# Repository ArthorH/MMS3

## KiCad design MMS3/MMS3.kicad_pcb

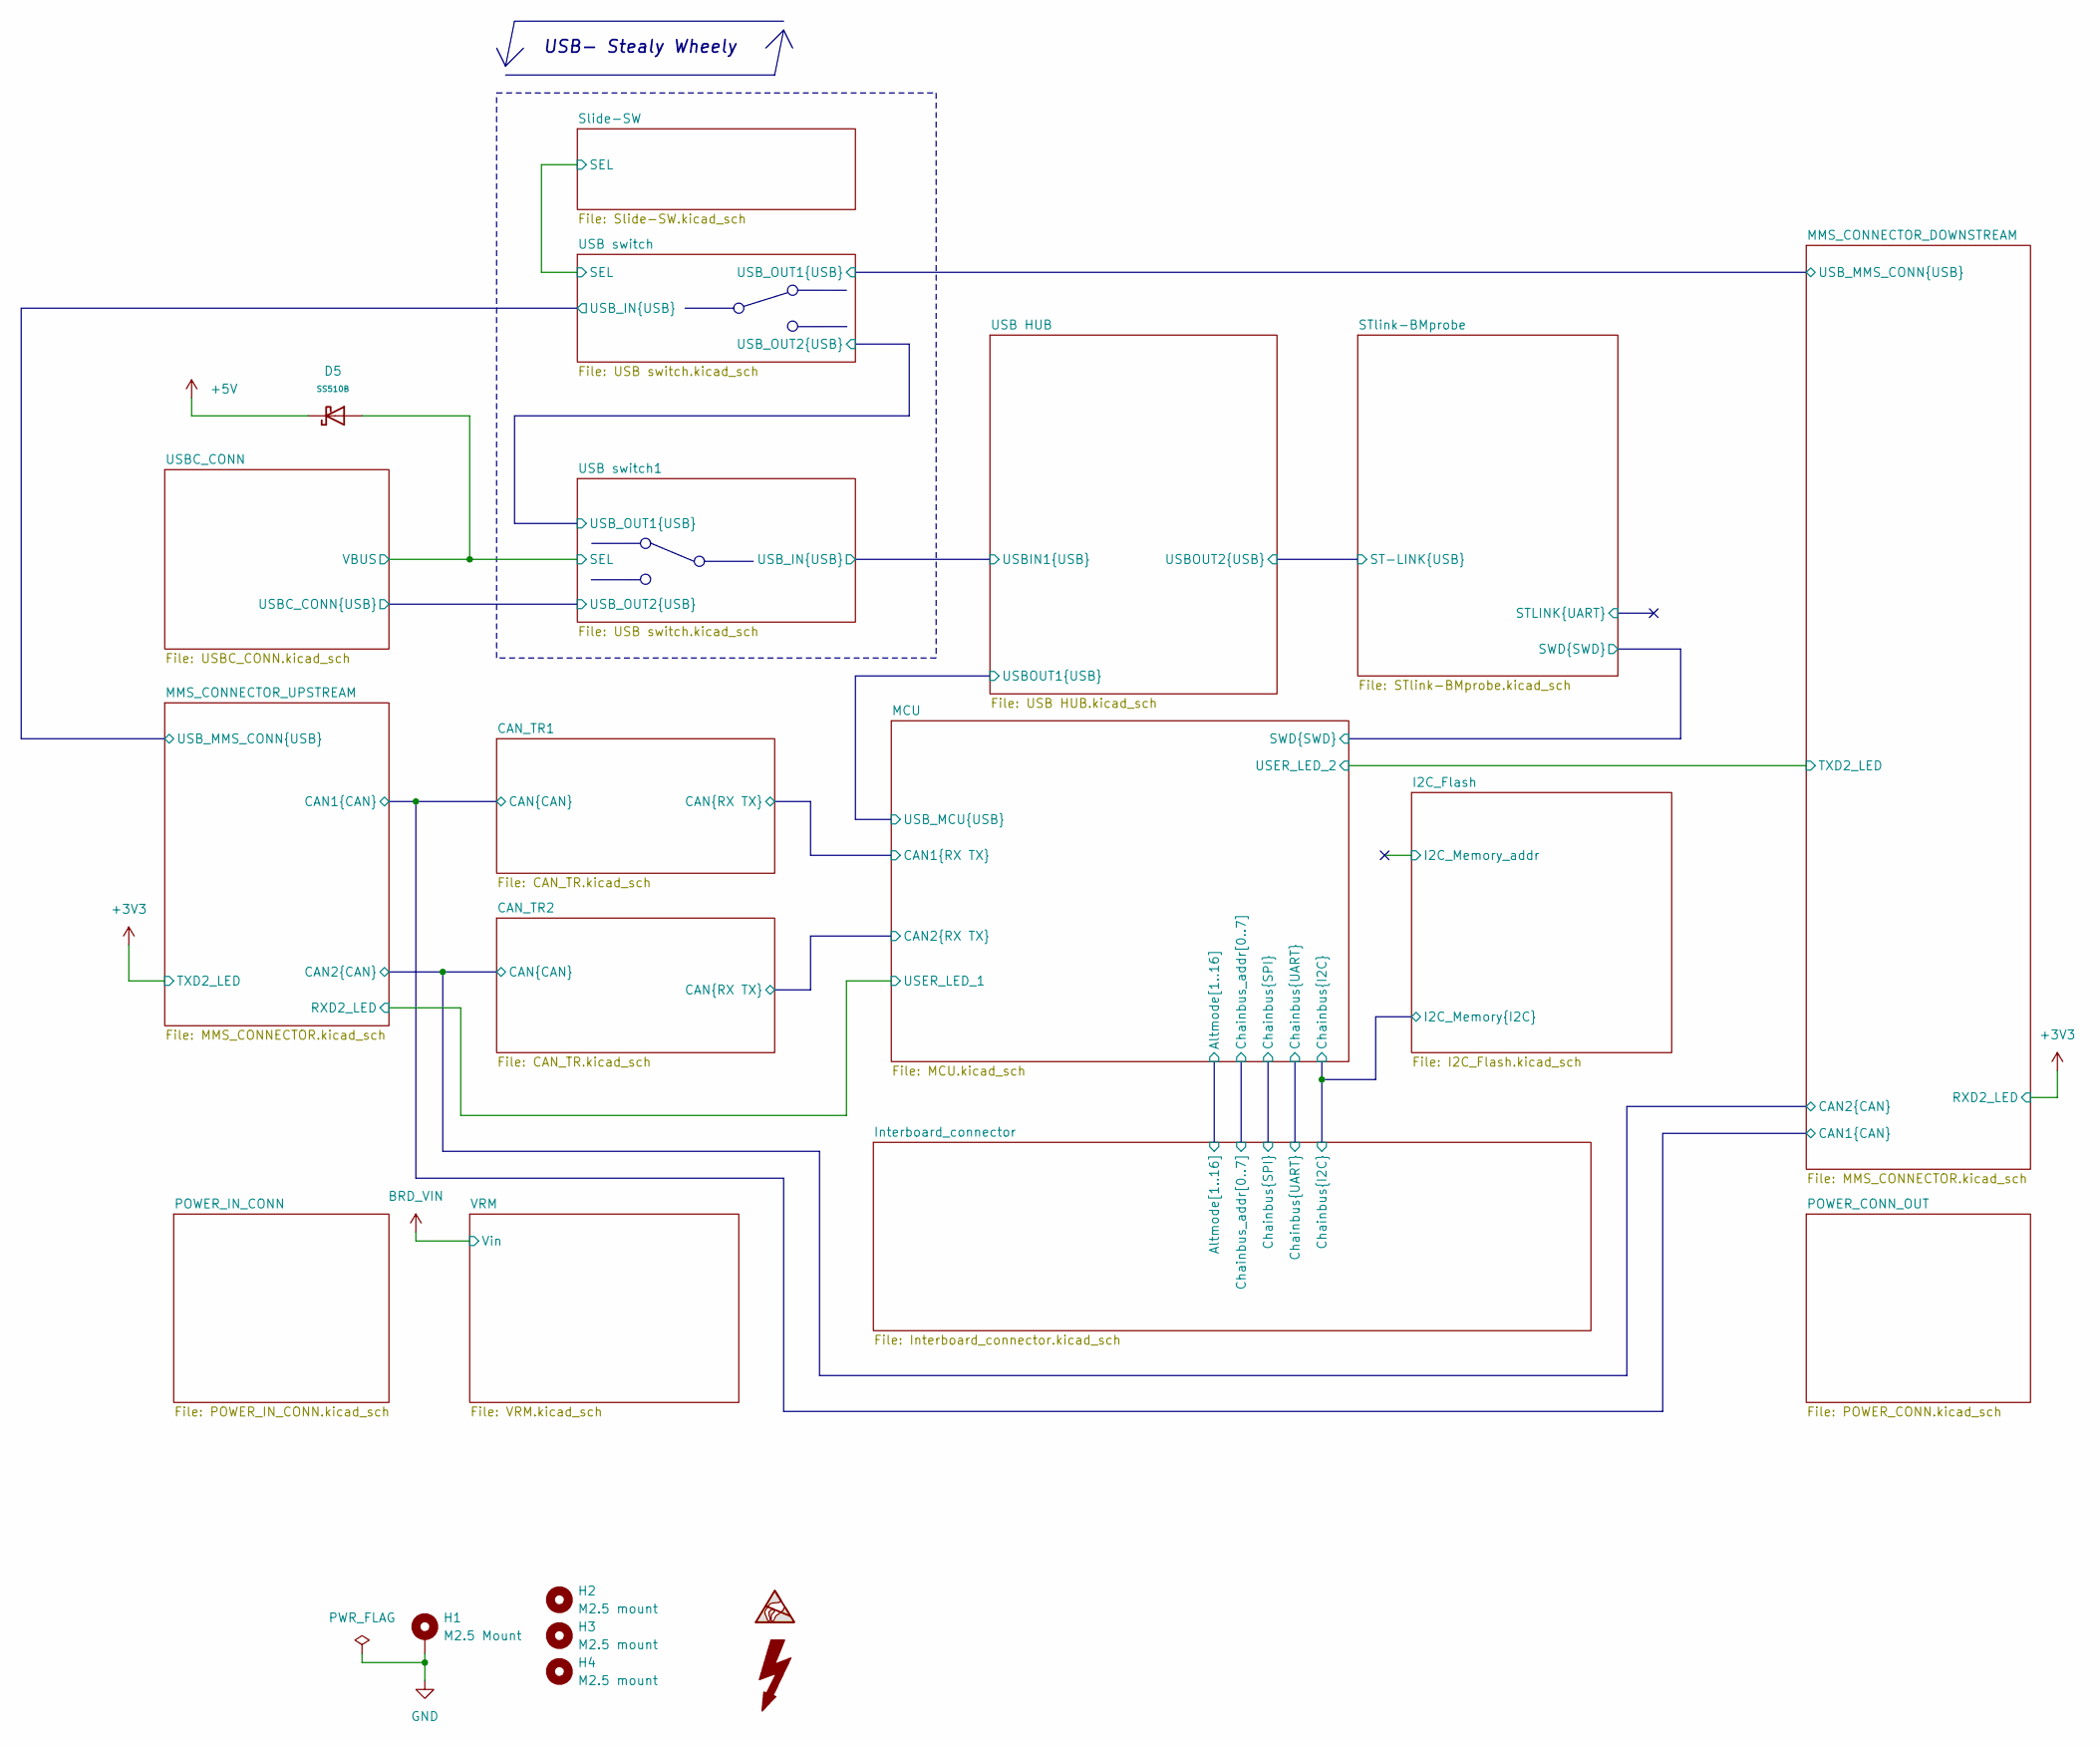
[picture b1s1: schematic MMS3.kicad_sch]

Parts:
D5: SS510B; D_SMB; Forward Voltage (Vf@If) 0.85V@5.0A; Reverse Voltage (Vr) 100V; Part SS510B; LCSC C7420368
H1: M2.5 Mount; MountingHole_2.7mm_M2.5_DIN965_Pad_TopOnly
H2, H3, H4: M2.5 mount; MountingHole_2.7mm_M2.5

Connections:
+5V: D5.1; also elsewhere on the board
GND: H1.1 (1_1); also elsewhere on the board
VBUS: D5.2; also elsewhere on the board

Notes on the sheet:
USB- Stealy Wheely

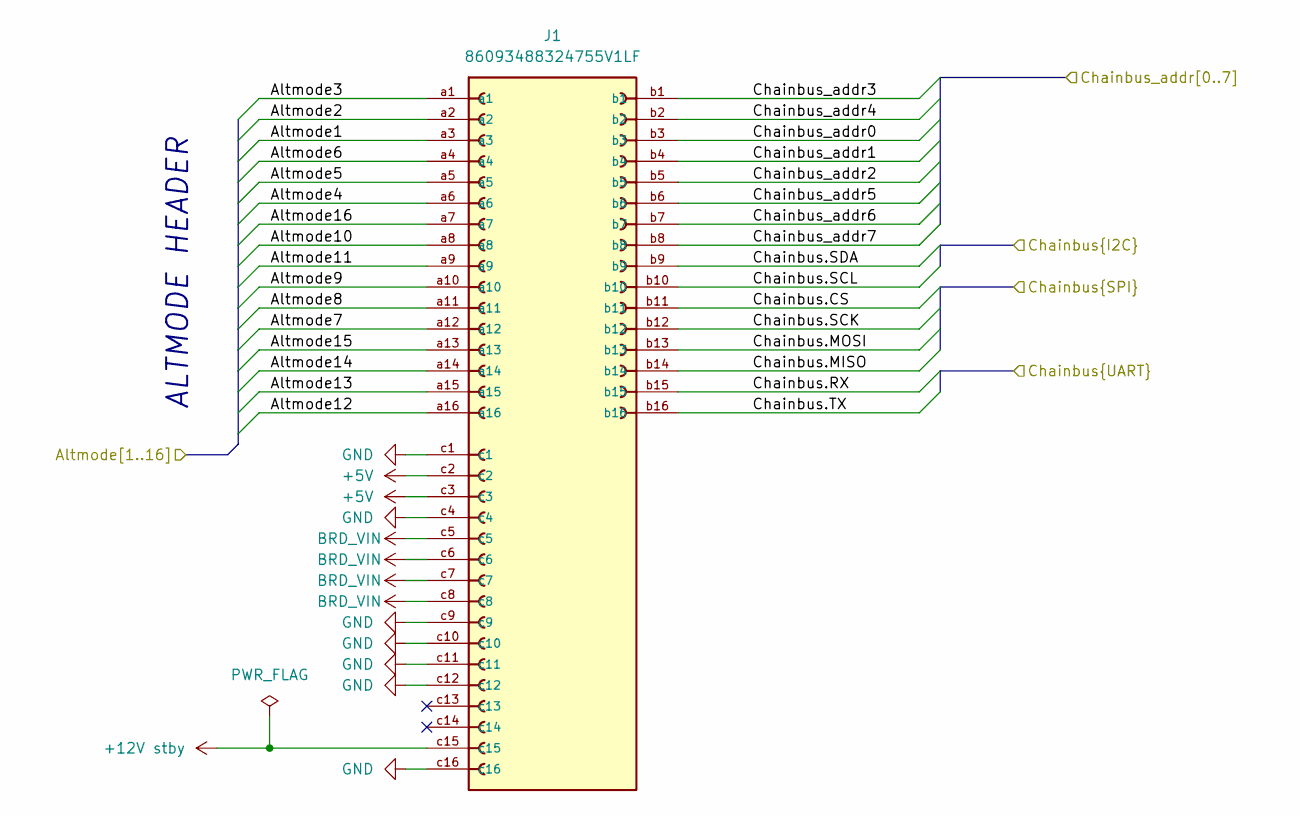
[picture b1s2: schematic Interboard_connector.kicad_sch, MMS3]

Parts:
J1: 86093488324755V1LF; DIN41612_C2_3x16_Female_Vertical_THT; PARTREV C; LCSC C5173373

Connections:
+5V: J1.c2, J1.c3; also elsewhere on the board
+12V stby: J1.c15; also elsewhere on the board
/I2C_Flash/I2C_Memory.SCL: J1.b10; also elsewhere on the board
/I2C_Flash/I2C_Memory.SDA: J1.b9; also elsewhere on the board
/Interboard_connector/Altmode1: J1.a3; also elsewhere on the board
/Interboard_connector/Altmode2: J1.a2; also elsewhere on the board
/Interboard_connector/Altmode3: J1.a1; also elsewhere on the board
/Interboard_connector/Altmode4: J1.a6; also elsewhere on the board
/Interboard_connector/Altmode5: J1.a5; also elsewhere on the board
/Interboard_connector/Altmode6: J1.a4; also elsewhere on the board
/Interboard_connector/Altmode7: J1.a12; also elsewhere on the board
/Interboard_connector/Altmode8: J1.a11; also elsewhere on the board
/Interboard_connector/Altmode9: J1.a10; also elsewhere on the board
/Interboard_connector/Altmode10: J1.a8; also elsewhere on the board
/Interboard_connector/Altmode11: J1.a9; also elsewhere on the board
/Interboard_connector/Altmode12: J1.a16; also elsewhere on the board
/Interboard_connector/Altmode13: J1.a15; also elsewhere on the board
/Interboard_connector/Altmode14: J1.a14; also elsewhere on the board
/Interboard_connector/Altmode15: J1.a13; also elsewhere on the board
/Interboard_connector/Altmode16: J1.a7; also elsewhere on the board
/Interboard_connector/Chainbus.CS: J1.b11; also elsewhere on the board
/Interboard_connector/Chainbus.MISO: J1.b14; also elsewhere on the board
/Interboard_connector/Chainbus.MOSI: J1.b13; also elsewhere on the board
/Interboard_connector/Chainbus.RX: J1.b15; also elsewhere on the board
/Interboard_connector/Chainbus.SCK: J1.b12; also elsewhere on the board
/Interboard_connector/Chainbus.TX: J1.b16; also elsewhere on the board
/Interboard_connector/Chainbus_addr0: J1.b3; also elsewhere on the board
/Interboard_connector/Chainbus_addr1: J1.b4; also elsewhere on the board
/Interboard_connector/Chainbus_addr2: J1.b5; also elsewhere on the board
/Interboard_connector/Chainbus_addr3: J1.b1; also elsewhere on the board
/Interboard_connector/Chainbus_addr4: J1.b2; also elsewhere on the board
/Interboard_connector/Chainbus_addr5: J1.b6; also elsewhere on the board
/Interboard_connector/Chainbus_addr6: J1.b7; also elsewhere on the board
/Interboard_connector/Chainbus_addr7: J1.b8; also elsewhere on the board
BRD_VIN: J1.c5, J1.c6, J1.c7, J1.c8; also elsewhere on the board
GND: J1.c1, J1.c4, J1.c9, J1.c10, J1.c11, J1.c12, J1.c16; also elsewhere on the board

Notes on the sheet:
ALTMODE HEADER

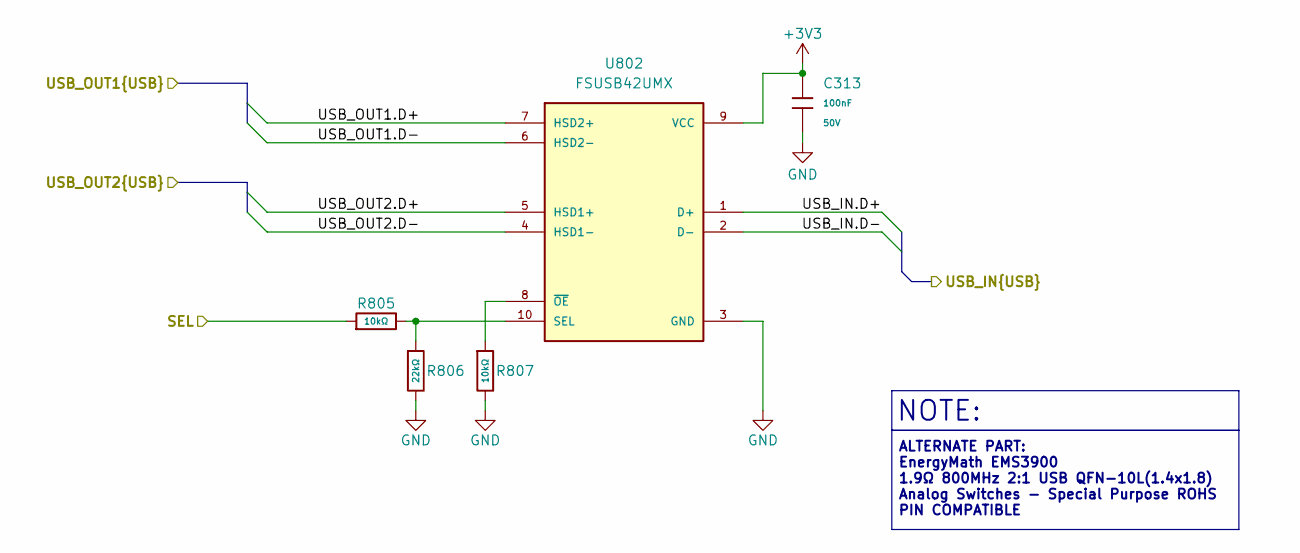
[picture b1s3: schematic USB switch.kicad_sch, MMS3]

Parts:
C313: 100nF; C_0402; Voltage Rated 50V; Tolerance ±10%; Part CL05B104KB54PNC; LCSC C307331
R805, R807: 10kΩ; R_0402; Overload Voltage (Max) 50V; Tolerance ±1%; Part 0402WGF1002TCE; LCSC C25744
R806: 22kΩ; R_0402; Overload Voltage (Max) 50V; Tolerance ±1%; Part 0402WGF2202TCE; LCSC C25768
U802: FSUSB42UMX; UQFN-10_1.4x1.8mm_P0.4mm; PARTREV 1.25; LCSC C11145

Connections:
+3V3: C313.1, U802.9 (VCC); also elsewhere on the board
/USB HUB/USBIN1.D+: U802.1 (D+); also elsewhere on the board
/USB HUB/USBIN1.D-: U802.2 (D-); also elsewhere on the board
/USB switch1/USB_OUT2.D+: U802.5 (HSD1+); also elsewhere on the board
/USB switch1/USB_OUT2.D-: U802.4 (HSD1-); also elsewhere on the board
/USB switch/USB_OUT2.D+: U802.7 (HSD2+); also elsewhere on the board
/USB switch/USB_OUT2.D-: U802.6 (HSD2-); also elsewhere on the board
GND: C313.2, R806.2, R807.2, U802.3 (GND); also elsewhere on the board
unnamed: R805.2, R806.1, U802.10 (SEL)
unnamed: R807.1, U802.8 (~OE)
VBUS: R805.1; also elsewhere on the board

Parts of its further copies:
C312: 100nF; C_0402; Voltage Rated 50V; Tolerance ±10%; Part CL05B104KB54PNC; LCSC C307331
R802, R804: 10kΩ; R_0402; Overload Voltage (Max) 50V; Tolerance ±1%; Part 0402WGF1002TCE; LCSC C25744
R803: 22kΩ; R_0402; Overload Voltage (Max) 50V; Tolerance ±1%; Part 0402WGF2202TCE; LCSC C25768
U801: FSUSB42UMX; UQFN-10_1.4x1.8mm_P0.4mm; PARTREV 1.25; LCSC C11145

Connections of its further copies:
+3V3: C312.1, U801.9 (VCC); also elsewhere on the board
/MMS_CONNECTOR_DOWNSTREAM/USB_MMS_CONN.D+: U801.7 (HSD2+); also elsewhere on the board
/MMS_CONNECTOR_DOWNSTREAM/USB_MMS_CONN.D-: U801.6 (HSD2-); also elsewhere on the board
/MMS_CONNECTOR_UPSTREAM/USB_MMS_CONN.D+: U801.1 (D+); also elsewhere on the board
/MMS_CONNECTOR_UPSTREAM/USB_MMS_CONN.D-: U801.2 (D-); also elsewhere on the board
/Slide-SW/SEL: R802.1; also elsewhere on the board
/USB switch/USB_OUT2.D+: U801.5 (HSD1+); also elsewhere on the board
/USB switch/USB_OUT2.D-: U801.4 (HSD1-); also elsewhere on the board
GND: C312.2, R803.2, R804.2, U801.3 (GND); also elsewhere on the board
unnamed: R802.2, R803.1, U801.10 (SEL)
unnamed: R804.1, U801.8 (~OE)

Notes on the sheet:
ALTERNATE PART: EnergyMath EMS3900 1.9Ω 800MHz 2:1 USB QFN-10L(1.4x1.8) Analog Switches - Special Purpose ROHS PIN COMPATIBLE
NOTE:

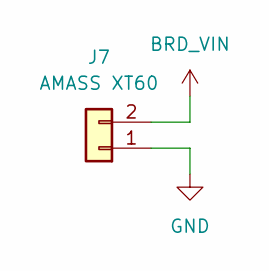
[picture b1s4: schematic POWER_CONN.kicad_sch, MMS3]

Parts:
J7: AMASS XT60; AMASS_XT60PW-F_1x02_P7.20mm_Horizontal; LCSC C428722

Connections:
BRD_VIN: J7.2; also elsewhere on the board
GND: J7.1; also elsewhere on the board

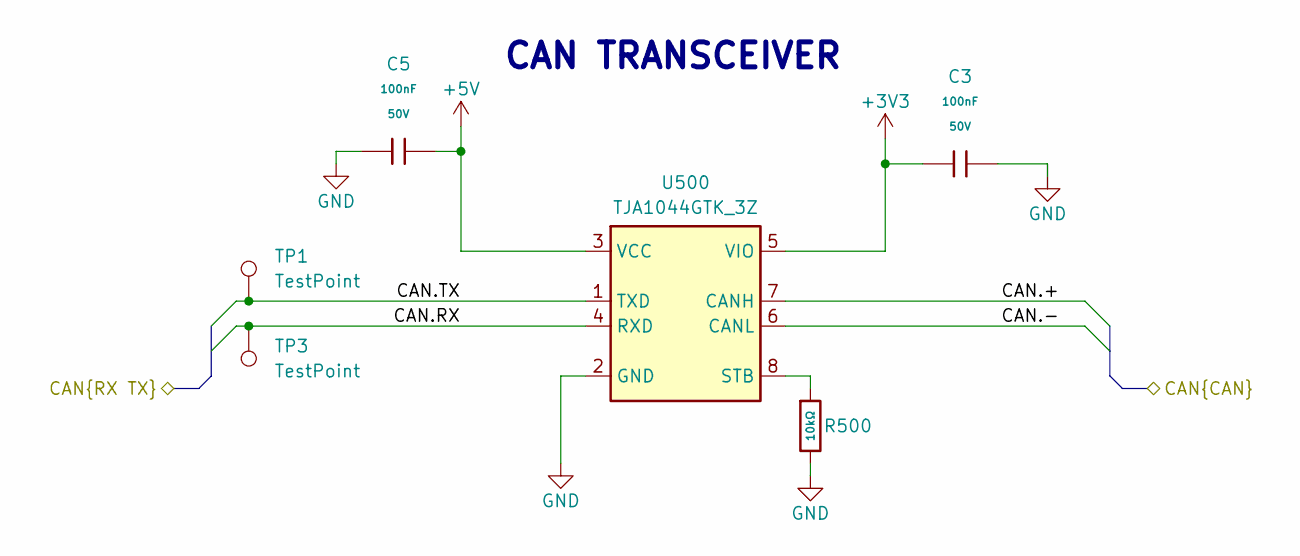
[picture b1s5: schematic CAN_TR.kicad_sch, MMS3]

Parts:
C3, C5: 100nF; C_0402; Voltage Rated 50V; Tolerance ±10%; Part CL05B104KB54PNC; LCSC C307331
R500: 10kΩ; R_0402; Overload Voltage (Max) 50V; Tolerance ±1%; Part 0402WGF1002TCE; LCSC C25744
TP1, TP3: TestPoint; TestPoint_Pad_D1.0mm
U500: TJA1044GTK_3Z; HVSON-8-1EP_3x3mm_P0.65mm_EP1.6x2.4mm; Manufacturer_Part_Number TJA1044GTK/3Z; LCSC C5215851

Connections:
+3V3: C3.1, U500.5 (VIO); also elsewhere on the board
+5V: C5.2, U500.3 (VCC); also elsewhere on the board
/CAN_TR1/CAN.+: U500.7 (CANH); also elsewhere on the board
/CAN_TR1/CAN.-: U500.6 (CANL); also elsewhere on the board
/CAN_TR1/CAN.RX: TP3.1 (1_1), U500.4 (RXD); also elsewhere on the board
/CAN_TR1/CAN.TX: TP1.1 (1_1), U500.1 (TXD); also elsewhere on the board
GND: C3.2, C5.1, R500.2, U500.2 (GND), U500.9 (EP); also elsewhere on the board
unnamed: R500.1, U500.8 (STB)

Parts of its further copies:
C4, C6: 100nF; C_0402; Voltage Rated 50V; Tolerance ±10%; Part CL05B104KB54PNC; LCSC C307331
R501: 10kΩ; R_0402; Overload Voltage (Max) 50V; Tolerance ±1%; Part 0402WGF1002TCE; LCSC C25744
TP2, TP4: TestPoint; TestPoint_Pad_D1.0mm
U501: TJA1044GTK_3Z; HVSON-8-1EP_3x3mm_P0.65mm_EP1.6x2.4mm; Manufacturer_Part_Number TJA1044GTK/3Z; LCSC C5215851

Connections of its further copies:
+3V3: C4.1, U501.5 (VIO); also elsewhere on the board
+5V: C6.2, U501.3 (VCC); also elsewhere on the board
/CAN_TR2/CAN.+: U501.7 (CANH); also elsewhere on the board
/CAN_TR2/CAN.-: U501.6 (CANL); also elsewhere on the board
/CAN_TR2/CAN.RX: TP4.1 (1_1), U501.4 (RXD); also elsewhere on the board
/CAN_TR2/CAN.TX: TP2.1 (1_1), U501.1 (TXD); also elsewhere on the board
GND: C4.2, C6.1, R501.2, U501.2 (GND), U501.9 (EP); also elsewhere on the board
unnamed: R501.1, U501.8 (STB)

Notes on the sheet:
CAN TRANSCEIVER

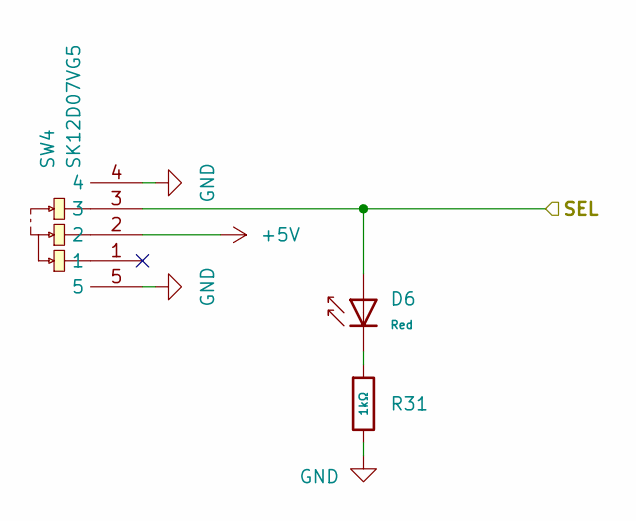
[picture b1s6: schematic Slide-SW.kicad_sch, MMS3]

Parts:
D6: Red; D_0603; Part KT-0603R; LCSC C2286
R31: 1kΩ; R_0402; Overload Voltage (Max) 50V; Tolerance ±1%; Part 0402WGF1001TCE; LCSC C11702
SW4: SK12D07VG5; SW-TH_SK12D07VG5-1; MPN SK12D07VG5; LCSC Part C431548

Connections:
+5V: SW4.2; also elsewhere on the board
/Slide-SW/SEL: D6.2, SW4.3; also elsewhere on the board
GND: R31.2, SW4.4, SW4.5; also elsewhere on the board
unnamed: D6.1, R31.1

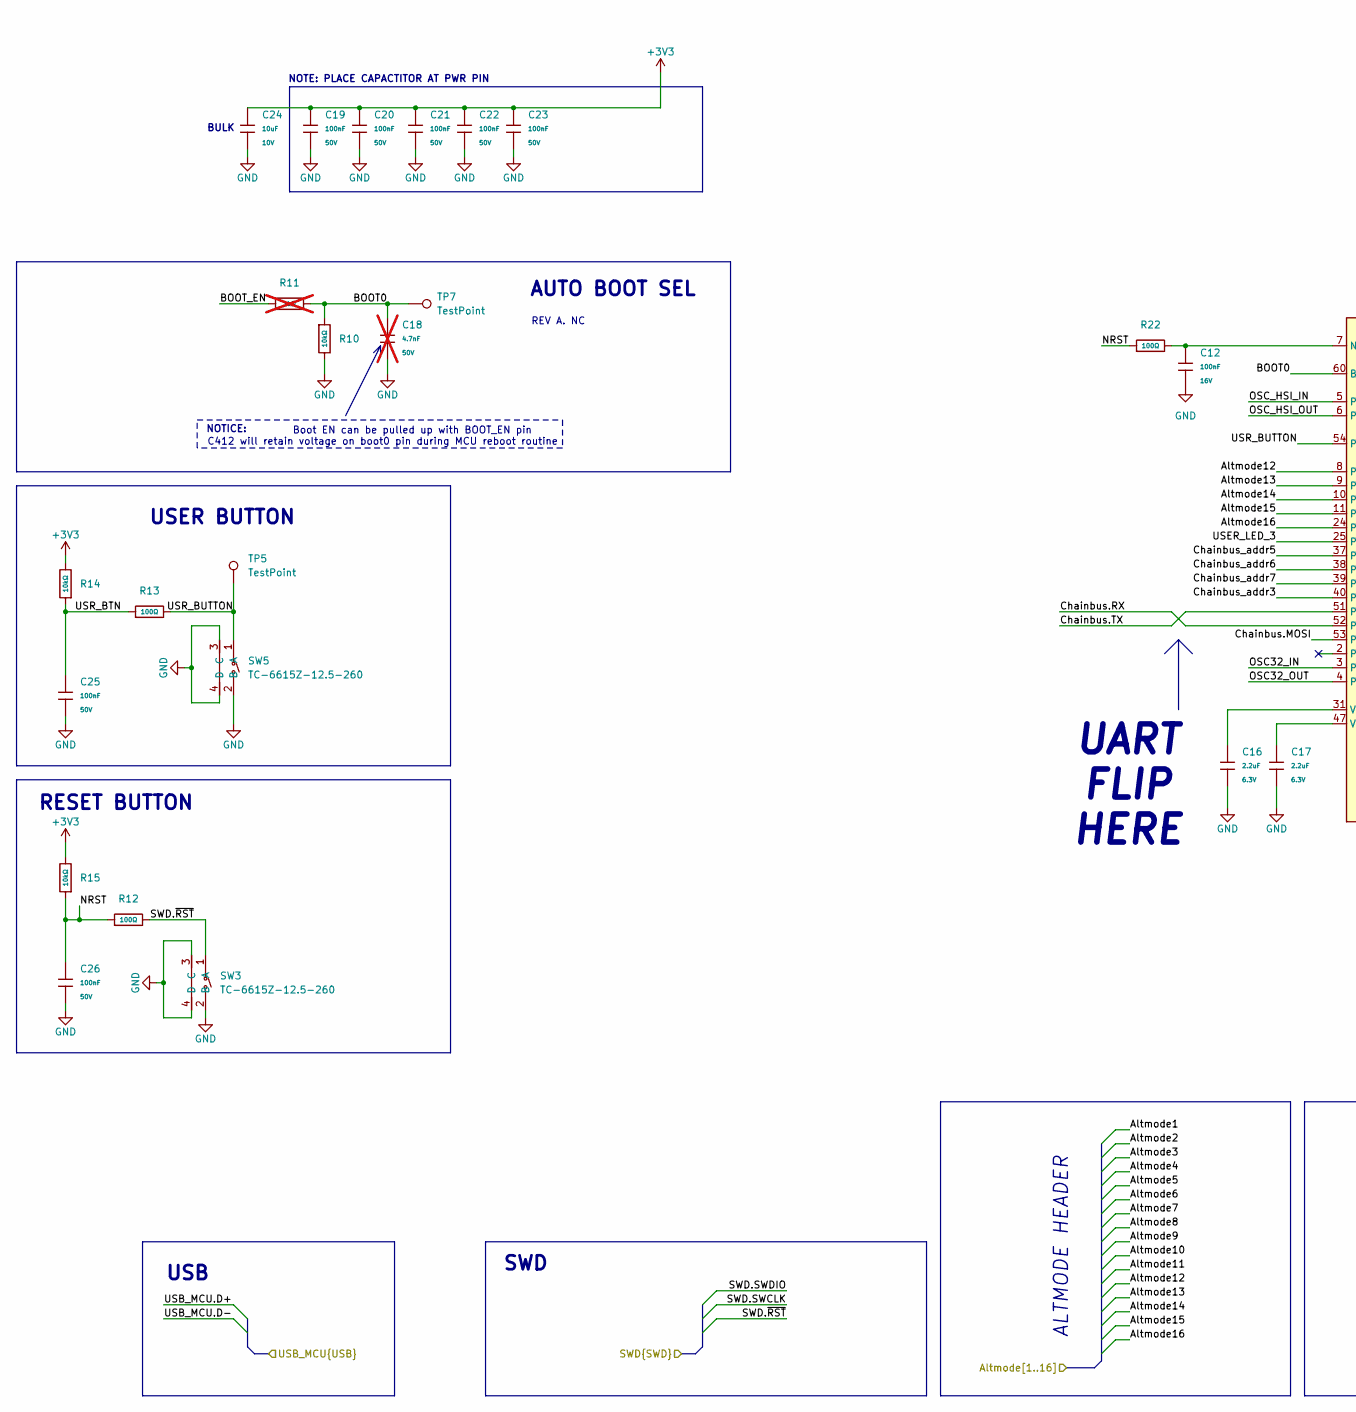
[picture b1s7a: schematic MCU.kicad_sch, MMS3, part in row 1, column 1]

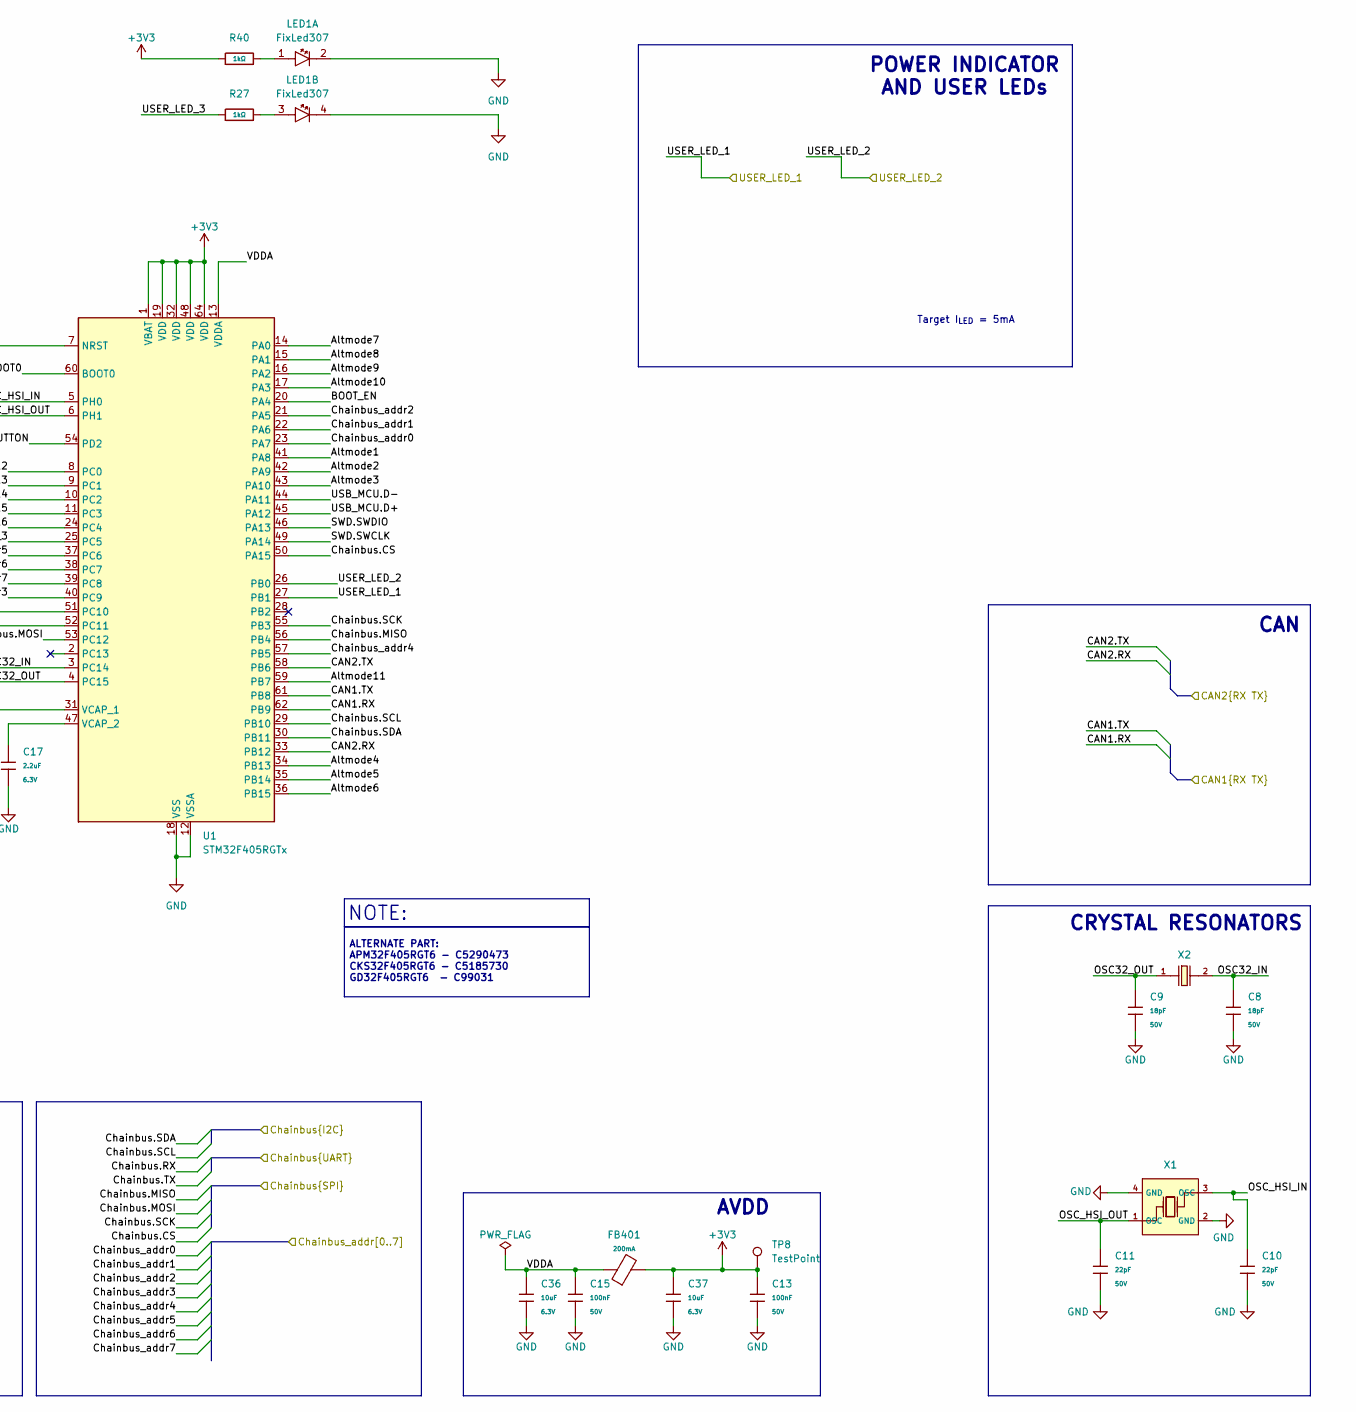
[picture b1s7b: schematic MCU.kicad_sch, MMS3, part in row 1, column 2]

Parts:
C8, C9: 18pF; C_0402; Voltage Rated 50V; Tolerance ±5%; Part 0402CG180J500NT; LCSC C1549
C10, C11: 22pF; C_0402; Voltage Rated 50V; Tolerance ±5%; Part 0402CG220J500NT; LCSC C1555
C12: 100nF; C_0402; Voltage Rated 16V; Tolerance ±10%; Part CL05B104KO5NNNC; LCSC C1525
C13, C15, C19, C20, C21, C22, C23, C25, C26: 100nF; C_0402; Voltage Rated 50V; Tolerance ±10%; Part CL05B104KB54PNC; LCSC C307331
C16, C17: 2.2uF; C_0402; Voltage Rated 6.3V; Tolerance ±20%; Part CL05A225MQ5NSNC; LCSC C12530
C18: 4.7nF; C_0402; Voltage Rated 50V; Tolerance ±10%; Part 0402B472K500NT; LCSC C1538; not fitted
C24: 10uF; C_0603; Voltage Rated 10V; Tolerance ±10%; Part CL10A106KP8NNNC; LCSC C19702
C36, C37: 10uF; C_0402; Voltage Rated 6.3V; Tolerance ±20%; Part CL05A106MQ5NUNC; LCSC C15525
FB401: FB_0603; Current Rating 200mA; Tolerance ±25%; Part GZ1608D601TF; LCSC C1002
LED1: FixLed307
R10, R14, R15: 10kΩ; R_0402; Overload Voltage (Max) 50V; Tolerance ±1%; Part 0402WGF1002TCE; LCSC C25744
R11: 1kΩ; R_0402; Overload Voltage (Max) 50V; Tolerance ±1%; Part 0402WGF1001TCE; LCSC C11702; not fitted
R12, R13, R22: 100Ω; R_0402; Overload Voltage (Max) 50V; Tolerance ±1%; Part 0402WGF1000TCE; LCSC C25076
R27, R40: 1kΩ; R_0402; Overload Voltage (Max) 50V; Tolerance ±1%; Part 0402WGF1001TCE; LCSC C11702
SW3, SW5: TC-6615Z-12.5-260; SW-TH_4P-L7.3-TC-6615Z-12.5-260; MPN TC-6615Z-12.5-260; LCSC Part C7528758
TP5, TP7, TP8: TestPoint; TestPoint_Pad_D1.0mm
U1: STM32F405RGTx; LQFP-64_10x10mm_P0.5mm; LCSC C15742
X1: X32258MOB4SI; OSC-SMD_4P-L3.2-W2.5-BL; Frequency Tolerance ±10ppm; Part X322525MOB4SI; LCSC C2682775
X2: Q13FC1350000400; FC-135R_L3.2-W1.5; Frequency Tolerance ±20ppm; Part Q13FC13500004; LCSC C97606

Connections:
+3V3: C13.1, C19.1, C20.1, C21.1, C22.1, C23.1, C24.1, C37.1, FB401.2, R14.2, R15.2, R40.1, TP8.1 (1_1), U1.1 (VBAT), U1.19 (VDD), U1.32 (VDD), U1.48 (VDD), U1.64 (VDD); also elsewhere on the board
/CAN_TR1/CAN.RX: U1.62 (PB9); also elsewhere on the board
/CAN_TR1/CAN.TX: U1.61 (PB8); also elsewhere on the board
/CAN_TR2/CAN.RX: U1.33 (PB12); also elsewhere on the board
/CAN_TR2/CAN.TX: U1.58 (PB6); also elsewhere on the board
/I2C_Flash/I2C_Memory.SCL: U1.29 (PB10); also elsewhere on the board
/I2C_Flash/I2C_Memory.SDA: U1.30 (PB11); also elsewhere on the board
/Interboard_connector/Altmode1: U1.41 (PA8); also elsewhere on the board
/Interboard_connector/Altmode2: U1.42 (PA9); also elsewhere on the board
/Interboard_connector/Altmode3: U1.43 (PA10); also elsewhere on the board
/Interboard_connector/Altmode4: U1.34 (PB13); also elsewhere on the board
/Interboard_connector/Altmode5: U1.35 (PB14); also elsewhere on the board
/Interboard_connector/Altmode6: U1.36 (PB15); also elsewhere on the board
/Interboard_connector/Altmode7: U1.14 (PA0); also elsewhere on the board
/Interboard_connector/Altmode8: U1.15 (PA1); also elsewhere on the board
/Interboard_connector/Altmode9: U1.16 (PA2); also elsewhere on the board
/Interboard_connector/Altmode10: U1.17 (PA3); also elsewhere on the board
/Interboard_connector/Altmode11: U1.59 (PB7); also elsewhere on the board
/Interboard_connector/Altmode12: U1.8 (PC0); also elsewhere on the board
/Interboard_connector/Altmode13: U1.9 (PC1); also elsewhere on the board
/Interboard_connector/Altmode14: U1.10 (PC2); also elsewhere on the board
/Interboard_connector/Altmode15: U1.11 (PC3); also elsewhere on the board
/Interboard_connector/Altmode16: U1.24 (PC4); also elsewhere on the board
/Interboard_connector/Chainbus.CS: U1.50 (PA15); also elsewhere on the board
/Interboard_connector/Chainbus.MISO: U1.56 (PB4); also elsewhere on the board
/Interboard_connector/Chainbus.MOSI: U1.53 (PC12); also elsewhere on the board
/Interboard_connector/Chainbus.RX: U1.52 (PC11); also elsewhere on the board
/Interboard_connector/Chainbus.SCK: U1.55 (PB3); also elsewhere on the board
/Interboard_connector/Chainbus.TX: U1.51 (PC10); also elsewhere on the board
/Interboard_connector/Chainbus_addr0: U1.23 (PA7); also elsewhere on the board
/Interboard_connector/Chainbus_addr1: U1.22 (PA6); also elsewhere on the board
/Interboard_connector/Chainbus_addr2: U1.21 (PA5); also elsewhere on the board
/Interboard_connector/Chainbus_addr3: U1.40 (PC9); also elsewhere on the board
/Interboard_connector/Chainbus_addr4: U1.57 (PB5); also elsewhere on the board
/Interboard_connector/Chainbus_addr5: U1.37 (PC6); also elsewhere on the board
/Interboard_connector/Chainbus_addr6: U1.38 (PC7); also elsewhere on the board
/Interboard_connector/Chainbus_addr7: U1.39 (PC8); also elsewhere on the board
/MCU/BOOT0: C18.1, R10.1, R11.2, TP7.1 (1_1), U1.60 (BOOT0)
/MCU/BOOT_EN: R11.1, U1.20 (PA4)
/MCU/NRST: C26.1, R12.1, R15.1, R22.1
/MCU/OSC32_IN: C8.1, U1.3 (PC14), X2.2
/MCU/OSC32_OUT: C9.1, U1.4 (PC15), X2.1
/MCU/OSC_HSI_IN: C10.1, U1.5 (PH0), X1.3 (OSC)
/MCU/OSC_HSI_OUT: C11.1, U1.6 (PH1), X1.1 (OSC)
/MCU/SWD.SWCLK: U1.49 (PA14); also elsewhere on the board
/MCU/SWD.SWDIO: U1.46 (PA13); also elsewhere on the board
/MCU/SWD.~RST: R12.2, SW3.1 (A); also elsewhere on the board
/MCU/USB_MCU.D+: U1.45 (PA12); also elsewhere on the board
/MCU/USB_MCU.D-: U1.44 (PA11); also elsewhere on the board
/MCU/USER_LED_1: U1.27 (PB1); also elsewhere on the board
/MCU/USER_LED_2: U1.26 (PB0); also elsewhere on the board
/MCU/USER_LED_3: R27.1, U1.25 (PC5)
/MCU/USR_BTN: C25.1, R13.1, R14.1
/MCU/USR_BUTTON: R13.2, SW5.1 (A), TP5.1 (1_1), U1.54 (PD2)
/MCU/VDDA: C15.1, C36.1, FB401.1, U1.13 (VDDA)
GND: C8.2, C9.2, C10.2, C11.2, C12.2, C13.2, C15.2, C16.2, C17.2, C18.2, C19.2, C20.2, C21.2, C22.2, C23.2, C24.2, C25.2, C26.2, C36.2, C37.2, LED1.2, LED1.4, R10.2, SW3.2 (B), SW3.3 (C), SW3.4 (D), SW5.2 (B), SW5.3 (C), SW5.4 (D), U1.12 (VSSA), U1.18 (VSS), U1.63 (VSS), X1.2 (GND), X1.4 (GND); also elsewhere on the board
unnamed: LED1.1, R40.2
unnamed: LED1.3, R27.2
unnamed: C12.1, R22.2, U1.7 (NRST)
unnamed: C16.1, U1.31 (VCAP_1)
unnamed: C17.1, U1.47 (VCAP_2)

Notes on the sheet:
Boot EN can be pulled up with BOOT_EN pin C412 will retain voltage on boot0 pin during MCU reboot routine
Target I_{LED} = 5mA
USER BUTTON
CRYSTAL RESONATORS
NOTE:
AVDD
RESET BUTTON
CAN
SWD
NOTE: PLACE CAPACTITOR AT PWR PIN
ALTERNATE PART: APM32F405RGT6 - C5290473 CKS32F405RGT6 - C5185730 GD32F405RGT6 - C99031
UART FLIP HERE
POWER INDICATOR AND USER LEDs
BULK
REV A. NC
ALTMODE HEADER
NOTICE:
USB
AUTO BOOT SEL

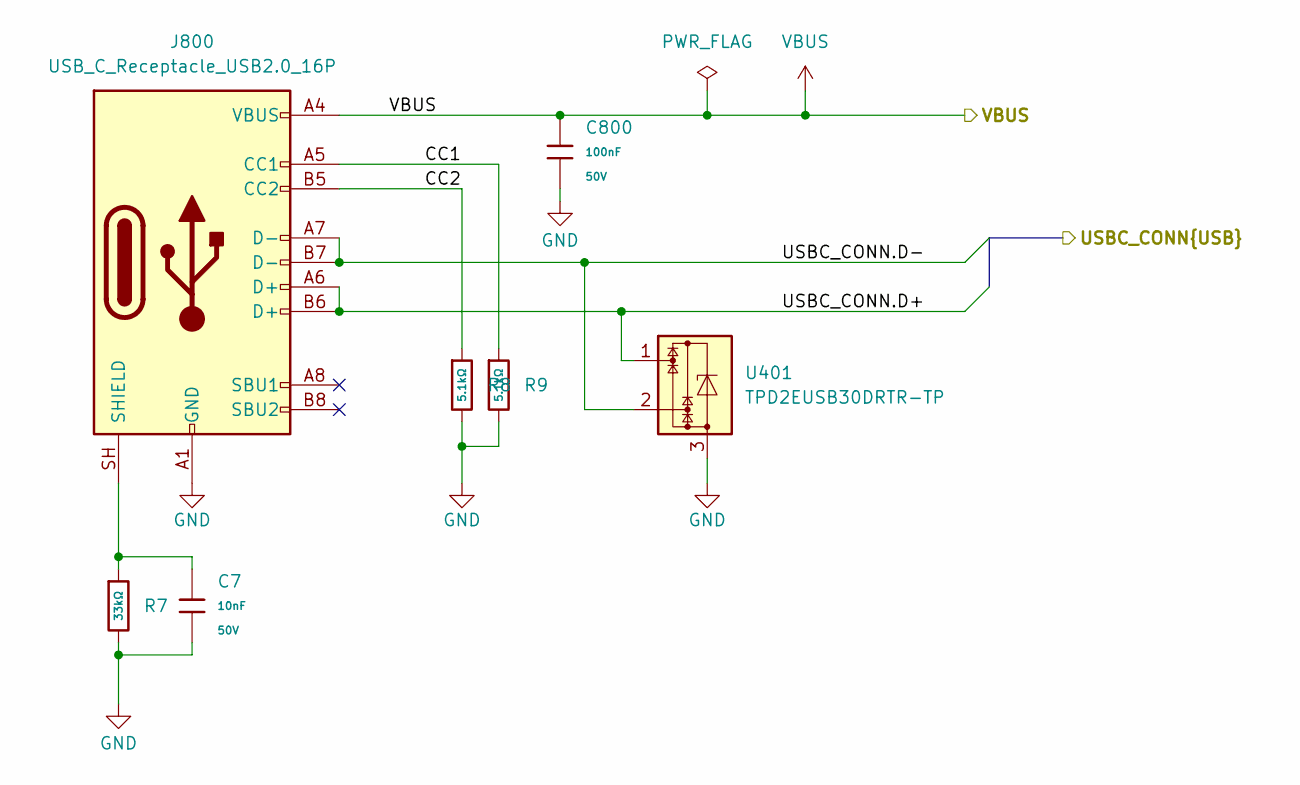
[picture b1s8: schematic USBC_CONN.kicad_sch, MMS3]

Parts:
C7: 10nF; C_0402; Voltage Rated 50V; Tolerance ±10%; Part CL05B103KB5NNNC; LCSC C15195
C800: 100nF; C_0402; Voltage Rated 50V; Tolerance ±10%; Part CL05B104KB54PNC; LCSC C307331
J800: USB_C_Receptacle_USB2.0_16P; USB_C_Receptacle_GCT_USB4105-xx-A_16P_TopMnt_Horizontal; LCSC C165948
R7: 33kΩ; R_0402; Overload Voltage (Max) 50V; Tolerance ±1%; Part 0402WGF3302TCE; LCSC C25779
R8, R9: 5.1kΩ; R_0402; Overload Voltage (Max) 50V; Tolerance ±1%; Part 0402WGF5101TCE; LCSC C25905
U401: TPD2EUSB30DRTR-TP; SOT-723; LCSC C2844720

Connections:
/USB switch1/USB_OUT2.D+: J800.A6 (D+), J800.B6 (D+), U401.1; also elsewhere on the board
/USB switch1/USB_OUT2.D-: J800.A7 (D-), J800.B7 (D-), U401.2; also elsewhere on the board
/USBC_CONN/CC1: J800.A5 (CC1), R9.1
/USBC_CONN/CC2: J800.B5 (CC2), R8.1
GND: C7.2, C800.2, J800.A1 (GND), J800.A12 (GND), J800.B1 (GND), J800.B12 (GND), R7.2, R8.2, R9.2, U401.3; also elsewhere on the board
unnamed: C7.1, J800.SH (SHIELD), R7.1
VBUS: C800.1, J800.A4 (VBUS), J800.A9 (VBUS), J800.B4 (VBUS), J800.B9 (VBUS); also elsewhere on the board

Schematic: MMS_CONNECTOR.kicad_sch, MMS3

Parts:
C1: 10nF; C_0402; Voltage Rated 50V; Tolerance ±10%; Part CL05B103KB5NNNC; LCSC C15195
J8: RJ45_LED_Shielded; RJ45_Amphenol_RJHSE538X
R1, R3: 220Ω; R_0402; Overload Voltage (Max) 50V; Tolerance ±1%; Part 0402WGF2200TCE; LCSC C25091
R5: 33kΩ; R_0402; Overload Voltage (Max) 50V; Tolerance ±1%; Part 0402WGF3302TCE; LCSC C25779
U4: TPD2EUSB30DRTR-TP; SOT-723; LCSC C2844720

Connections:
+3V3: R3.2; also elsewhere on the board
+12V stby: J8.6; also elsewhere on the board
/CAN_TR1/CAN.+: J8.2; also elsewhere on the board
/CAN_TR1/CAN.-: J8.1; also elsewhere on the board
/CAN_TR2/CAN.+: J8.5; also elsewhere on the board
/CAN_TR2/CAN.-: J8.4; also elsewhere on the board
/MCU/USER_LED_2: R1.2; also elsewhere on the board
/MMS_CONNECTOR_DOWNSTREAM/USB_MMS_CONN.D+: J8.8, U4.2; also elsewhere on the board
/MMS_CONNECTOR_DOWNSTREAM/USB_MMS_CONN.D-: J8.7, U4.1; also elsewhere on the board
GND: C1.2, J8.3, J8.9, J8.11, R5.2, U4.3; also elsewhere on the board
unnamed: C1.1, J8.SH, R5.1
unnamed: J8.10, R1.1
unnamed: J8.12, R3.1

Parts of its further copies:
C2: 10nF; C_0402; Voltage Rated 50V; Tolerance ±10%; Part CL05B103KB5NNNC; LCSC C15195
J9: RJ45_LED_Shielded; RJ45_Amphenol_RJHSE538X
R2, R4: 220Ω; R_0402; Overload Voltage (Max) 50V; Tolerance ±1%; Part 0402WGF2200TCE; LCSC C25091
R6: 33kΩ; R_0402; Overload Voltage (Max) 50V; Tolerance ±1%; Part 0402WGF3302TCE; LCSC C25779
U5: TPD2EUSB30DRTR-TP; SOT-723; LCSC C2844720

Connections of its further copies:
+3V3: R2.2; also elsewhere on the board
+12V stby: J9.6; also elsewhere on the board
/CAN_TR1/CAN.+: J9.2; also elsewhere on the board
/CAN_TR1/CAN.-: J9.1; also elsewhere on the board
/CAN_TR2/CAN.+: J9.5; also elsewhere on the board
/CAN_TR2/CAN.-: J9.4; also elsewhere on the board
/MCU/USER_LED_1: R4.2; also elsewhere on the board
/MMS_CONNECTOR_UPSTREAM/USB_MMS_CONN.D+: J9.8, U5.2; also elsewhere on the board
/MMS_CONNECTOR_UPSTREAM/USB_MMS_CONN.D-: J9.7, U5.1; also elsewhere on the board
GND: C2.2, J9.3, J9.9, J9.11, R6.2, U5.3; also elsewhere on the board
unnamed: C2.1, J9.SH, R6.1
unnamed: J9.10, R2.1
unnamed: J9.12, R4.1
